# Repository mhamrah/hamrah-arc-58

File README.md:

# Hamrah Arc 58

A low-profile, split 58-input keyboard built around Kailh Choc v1 hotswap
switches, KEEBD Helios RP2040 controllers, per-key RGB, OLEDs, clickable
encoders, and a fully reversible PCB. The design keeps the approved Sofle Choc
6x4 column-staggered field and replaces the original bottom cluster with a
four-key inward/downward Arc thumb fan.

Each half has 29 press inputs:

- 24 column-staggered main keys;
- four Arc thumb keys; and
- one clickable rotary encoder.

## Layout preview

[Open the full-size SVG](output/keyboard-layout.svg)

## Geometry

All dimensions live in `layout.config.json`.

| Parameter | Value |
| --- | ---: |
| Main matrix pitch | 19.05 x 19.05 mm |
| Choc plate cutout | 14 x 14 mm |
| Specified Choc v1 keycap | 16.5 x 16.5 mm |
| Choc keys per half | 28 |
| Clickable encoders per half | 1 |
| EC11 body plate cutout | 12.5 x 12.5 mm |
| Encoder knob-to-C6 / knob-to-inner-edge gap | 9.17 mm / 9.17 mm |
| Thumb center spacing | 21.25 mm |
| T1 outward offset from C5/C6 midpoint | 1.0 mm |
| Conservative thumb envelope / minimum gap | 18 x 18 mm / 0.5 mm |
| Thumb key rotations | 10, 30, 45, 55 degrees |
| Mounting holes per half | 6 x 2.2 mm |

## Generate and verify

Node.js 18 or newer and KiCad 9 are required.

```sh
npm run generate
npm run verify
npm run generate:enclosures
```

Generation creates the mirrored layout, a US Letter 1:1 paper test, exact key
positions, and left/right top and bottom plate SVG/DXF files under `output/`.
Print the paper test at Actual Size / 100% and confirm its calibration bar is
exactly 50 mm before ordering plates.

`generate:enclosures` additionally creates vendor ZIP packages for 1.5 mm
acrylic top plates, 3 mm acrylic bottom plates, and a 6061-T6 machined aluminum
case under `output/manufacturing/`. It uses `uv` with Python 3.12 to run the
CadQuery solid-model generator. Material, tolerances, fit-coupon instructions,
and the nominal hardware stack are documented in
[`hardware/ENCLOSURES.md`](hardware/ENCLOSURES.md).

The single native PCB project is:

```text
hardware/kicad/arc58-reversible.kicad_pro
hardware/kicad/arc58-reversible.kicad_pcb
```

Order two copies of the same Rev Gamma PCB. In the assembled keyboard, the B.Cu
face points toward the keycaps on the left half and the F.Cu face points toward
the keycaps on the right half. Detailed component-side selection, verified pin
mapping, DRC status, and safety notes are in `hardware/README.md`; the pair BOM is
`hardware/BOM-REV-GAMMA.csv`.

Rev Gamma supersedes Rev Beta without changing any switch center, plate, or
case geometry. It moves D26-D29 into solder-friendly positions beside the four
thumb sockets, gives the inner D29 extra socket-body clearance, and reroutes
the affected reversible copper with no jumper. Rev Beta can be electrically
prototyped, but its inner thumb diode crowds the Choc socket and its outer
thumb diodes require awkward long reaches; do not reorder it.

Do not build or reorder Rev Alpha: it has no routed optical/package apertures
for per-key RGB, its TRRS jack points toward the encoder instead of the cable
exit, and its four thumb-switch axes are mirrored to the wrong physical
angles. Its 20.5 mm thumb centers also fail the conservative 18 x 18 mm
clearance requirement. Rev Alpha may be electrically bench-tested with every
RGB LED omitted and without an enclosure, but it does not implement the
intended keyboard.

## Prototype status

The routed board passes the repository's structural and electrical checks:
zero unrouted connections and zero shorts, crossings, or fabrication-clearance
violations. Its Edge.Cuts layer contains 28 closed 3.6 x 3.1 mm RGB apertures
per half, and the inner-edge TRRS jack/plate geometry provides a 10 mm cable
opening. The switch locator holes independently verify the assembled thumb
axes: +10, +30, +45, and +55 degrees on the B.Cu/left half, mirrored to -10,
-30, -45, and -55 degrees on the F.Cu/right half. T3 eases five degrees outward;
T4 eases fifteen degrees outward and its center moves 3.14 mm toward the side
and 2.59 mm upward from the former 70-degree position. The thumb centers remain
21.25 mm apart and preserve more than 0.5 mm nominal clearance for a
conservative 18 x 18 mm keycap envelope. The specified 16.5 x 16.5 mm caps
retain approximately 2.3 mm minimum clearance, with the T3-T4 gap increased to
approximately 3.44 mm. QMK is configured for
Helios, a one-wire TRRS split, OLED, encoder, and a 28+28 RGB Matrix. The
default firmware also compiles successfully against current upstream QMK; the
ignored local UF2 is generated at
`output/firmware/arc58-rev-gamma-default.uf2`.

This is still a prototype until a fabricated pair passes
`hardware/BRING-UP-CHECKLIST.md`. Choc switches plug into soldered hotswap
sockets; the switches themselves are not soldered to the PCB. Use a small
prototype order and verify switch/plate fit, diode and LED orientation, USB
current, every key, both encoders, both OLEDs, RGB, and the split link before a
larger run.

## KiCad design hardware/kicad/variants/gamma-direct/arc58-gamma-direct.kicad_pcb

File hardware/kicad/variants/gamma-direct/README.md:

# Arc 58 Gamma-D — direct RGB prototype

This variant removes the board-mounted U2 level shifter. It is a prototype for electrical qualification, not a production-qualified release. The original Gamma board is retained in the repository.

## Circuit

RP2040 GPIO0 / Pro Micro D3 / U1 pad 1 → RGB_MCU → R1 pad 1 → 330 ohm → R1 pad 2 → RGB_LED_IN → SW1 LED DIN pin 4 → remaining LED chain.

U2 and its footprint are removed. Copper replaces the U2 input/output connection. Obsolete supply/ground branch stubs were cleaned up and zones refilled. R1 remains 0603, nominal 330 ohm; 220 ohm is an acceptable substitute. No user-installed bypass jumper is needed. Do not substitute 10 kohm.

C1 remains available as an additional 100 nF supply bypass capacitor; it is optional for this direct variant. Populate C2, 47 uF / 10 V ceramic / 1206, for bulk RGB supply bypassing. The existing board still lacks per-LED bypass capacitors. LEDs remain on the 5 V rail. Existing firmware continues to use D3/GPIO0, and its brightness limit remains 32.

All other component positions and pad connections are unchanged. Existing plate and case geometry are retained. Silkscreen identifies this variant as GAMMA-D. BOM quantities cover both halves.

## How comparable keyboards avoid U2

The original Sofle RGB build guide specifies an ATmega32U4 Pro Micro or Elite-C. The usual 5 V versions already output 5 V logic, so they do not need a separate 3.3-to-5 V buffer. Using an RP2040 replacement changes this assumption.

Some 5 V addressable LEDs accept 3.3 V data in practice. Adafruit documents this behavior, including SK6812 devices, but it depends on device type, individual tolerances and operating conditions. A working prototype is useful evidence, not a guarantee for every future LED batch.

A design with guaranteed input compatibility can instead use an exact LED part whose specified input-high threshold accepts the controller's guaranteed output-high level, or obtain a shifted signal from a suitable controller pin. Neither is assumed in this variant. GPIO0 on the currently targeted controller remains the data source.

Sources:
- https://josefadamcik.github.io/SofleKeyboard/build_guide_rgb.html
- https://learn.adafruit.com/adafruit-neopixel-uberguide/logic-level
- https://docs.qmk.fm/drivers/ws2812

## Verification

- KiCad 10.0.5 DRC: zero violations and zero unconnected items; see DRC.json.
- Compared the original and variant: U2 is the only removed footprint; every remaining footprint position, orientation and pad net is preserved except the intended R1 pad 1 change to RGB_MCU. Both reversible SW1 DIN pads are preserved.
- Full repository structural check is NOT passing: both original Gamma and Gamma-D stop at the same existing D29 placement mismatch (130.839,137.603 mm versus expected 133.593,140.430 mm). This revision does not change D29. Checks after that failure have not run.
- No physical RGB, signal-integrity, temperature, or manufacturing qualification has been performed. No schematic exists in the source repository; this package contains the PCB project and BOM, not a new schematic.

Before ordering a batch, test the original board with the U2 2-to-4 jumper and R1 installed: that implements the same direct-drive concept. Confirm all LEDs on both halves across cold starts, different colors/animations, and normal USB power sources. If unreliable, keep the original buffered design or qualify a specified lower-threshold LED/controller solution.

## Files and repository

Open arc58-gamma-direct.kicad_pro in KiCad. The PCB includes its footprints; external 3D model libraries may be needed for 3D viewing. No Gerber manufacturing package is included.

Repository copy: hardware/kicad/variants/gamma-direct/.

The repository verifier accepts:

    python3 scripts/verify-kicad-board.py --direct-rgb --board hardware/kicad/variants/gamma-direct/arc58-gamma-direct.kicad_pcb

Use KiCad's Python environment for that command. For the DRC:

    kicad-cli pcb drc --format json --output direct-drc.json hardware/kicad/variants/gamma-direct/arc58-gamma-direct.kicad_pcb

The original generate:fab command still targets the original Gamma board.

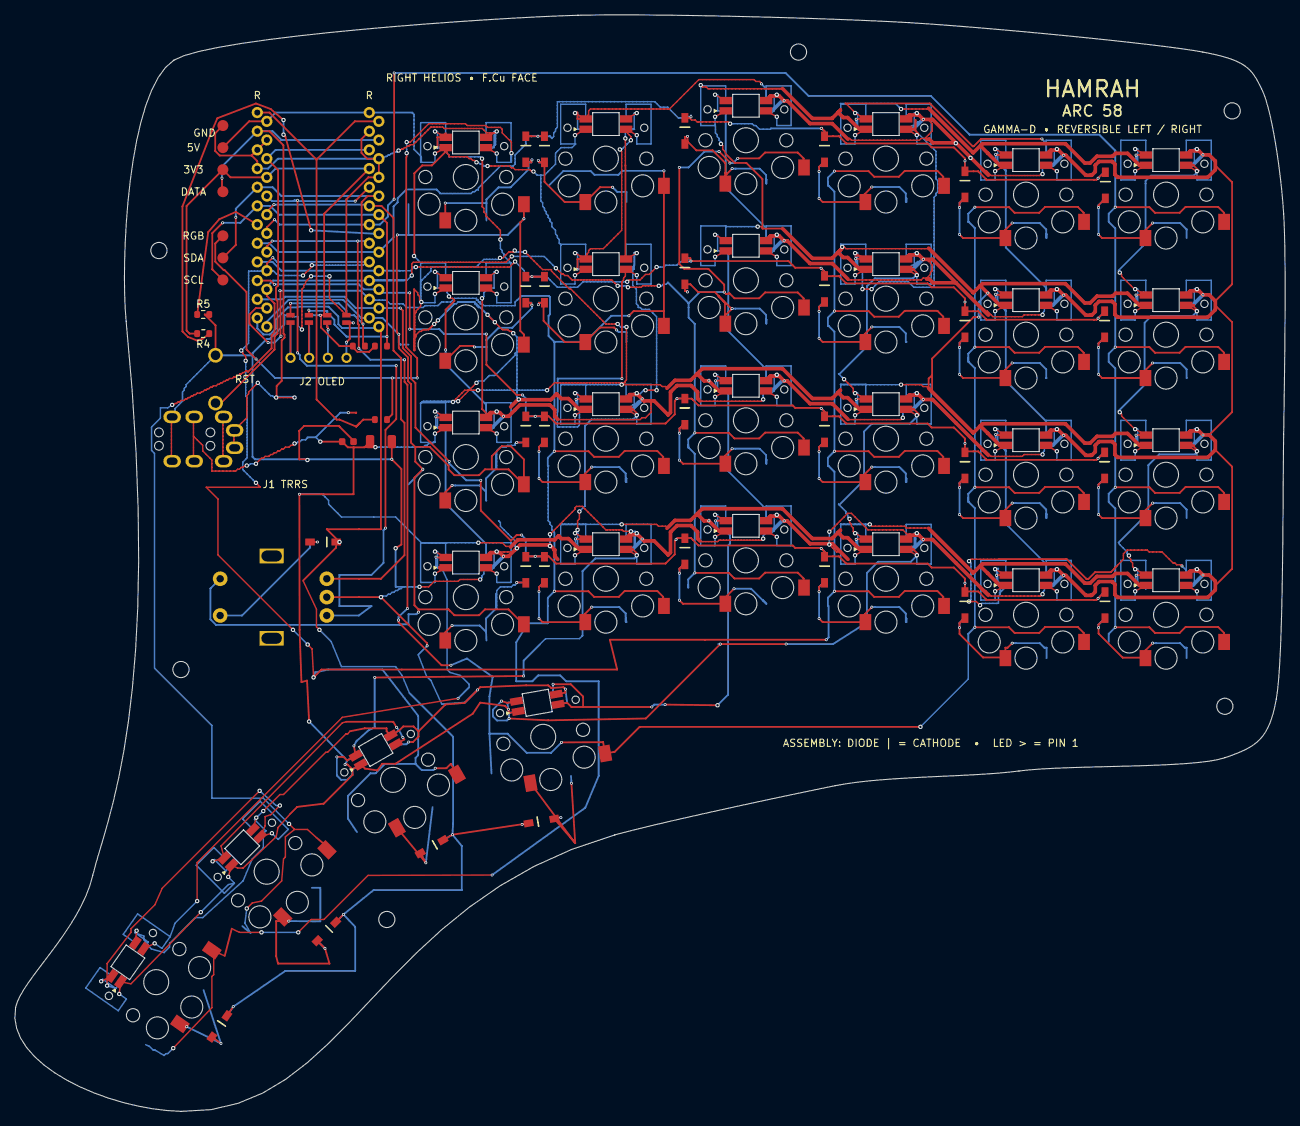
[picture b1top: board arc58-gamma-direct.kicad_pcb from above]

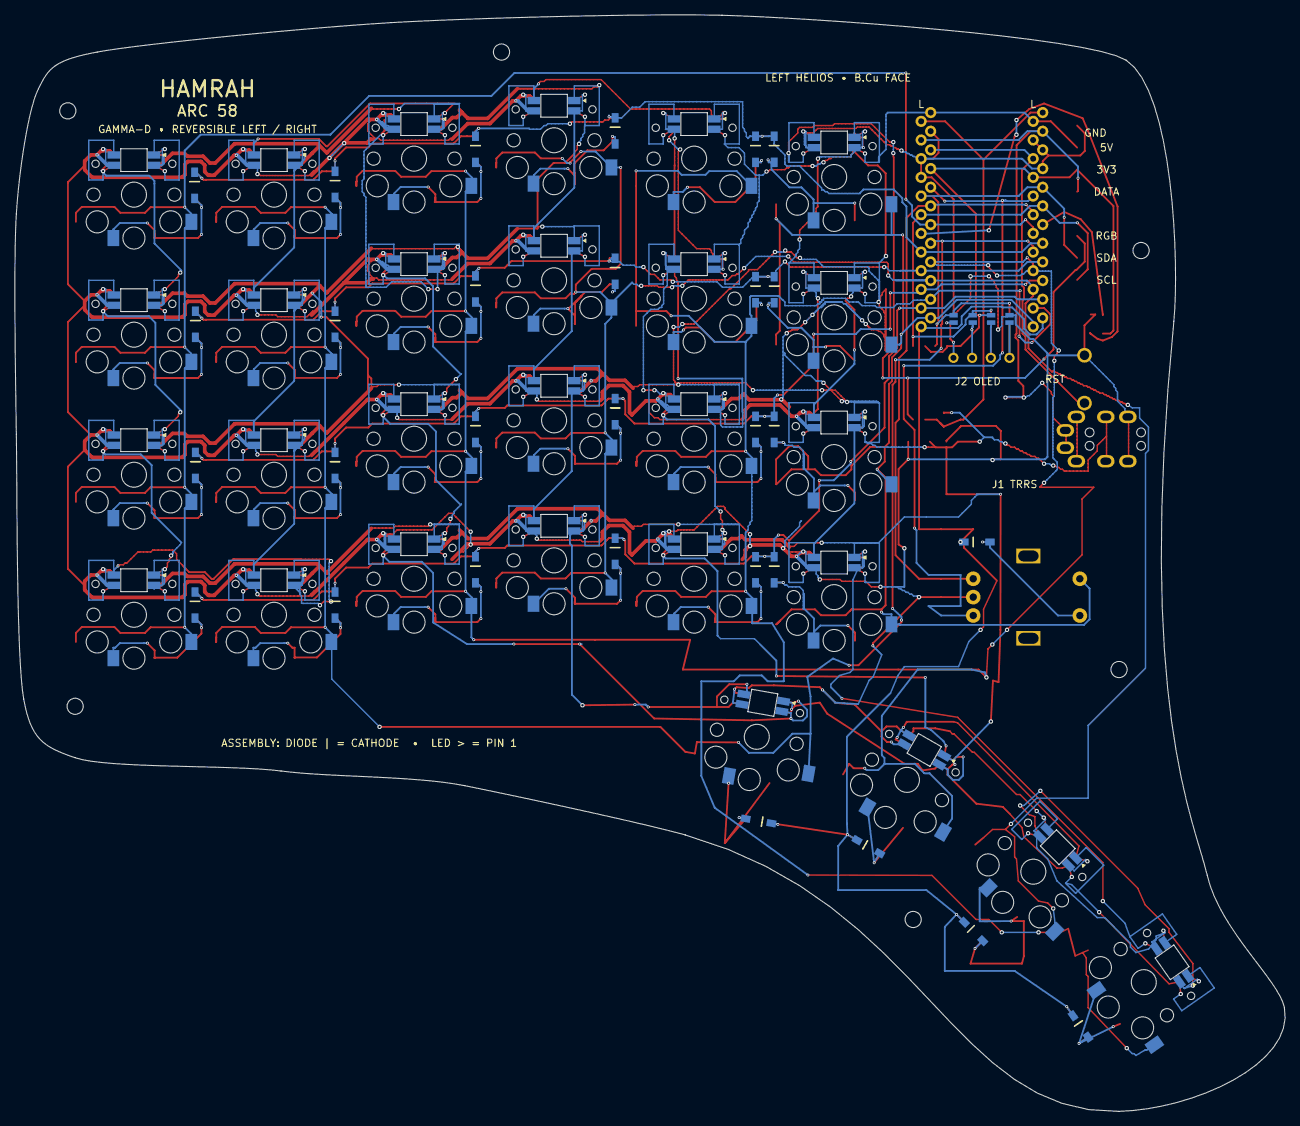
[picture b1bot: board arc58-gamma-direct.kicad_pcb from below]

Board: 2 copper layers, 172.8 x 149.2 mm, 90 parts (4 on the bottom side), 84 nets.

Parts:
C1: 100nF; C_0603_1608Metric
C2: 47uF 10V; C_1206_3216Metric
D1, D2, D3, D4, D5, D6, D7, D8, D9, D10, D11, D12, D13, D14, D15, D16, D17, D18, D19, D20, D21, D22, D23, D24, D25, D26, D27, D28, D29: D; Reversible_Diode_SOD123
H1, H2, H3, H4, H5, H6: MountingHole_2.2mm_M2
J1: MJ-4PP-9_Reversible; CON_MJ-4PP-9_Reversible
J2: SSD1306 OLED 128x32; OLED_4Pin
JP1, JP2, JP3, JP4, JP5, JP6, JP7, JP8: Jumper_NO_Small; Jumper
R1: 330R; R_0603_1608Metric
R2, R3: 4.7k; R_0603_1608Metric
R4, R5: 10k; R_0603_1608Metric
RST1: RESET; TACT_SWITCH_TVBP06
SW1, SW2, SW3, SW4, SW5, SW6, SW7, SW8, SW9, SW10, SW11, SW12, SW13, SW14, SW15, SW16, SW17, SW18, SW19, SW20, SW21, SW22, SW23, SW24, SW26, SW27, SW28, SW29: SW_PUSH_LED; Sofle_Choc_Hotswap_SK6812MINI-E_Reversible
SW25: EC11_Clickable_H20mm_T18; RotaryEncoder_Alps_EC11E-Switch_Vertical_H20mm-keebio_modif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
TP1, TP2, TP3, TP4, TP6, TP7, TP8: TestPoint_Pad_D1.5mm
U1: KEEBD Helios RP2040; ProMicro

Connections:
COL0: SW6.6, SW12.6, SW18.6, SW24.6, U1.18
COL1: SW5.6, SW11.6, SW17.6, SW23.6, SW29.6, U1.17
COL2: SW4.6, SW10.6, SW16.6, SW22.6, SW28.6, U1.16
COL3: SW3.6, SW9.6, SW15.6, SW21.6, SW27.6, U1.15
COL4: SW2.6, SW8.6, SW14.6, SW20.6, SW26.6, U1.14
COL5: SW1.6, SW7.6, SW13.6, SW19.6, SW25.S1, U1.13
ENC_A: SW25.A, U1.20
ENC_B: SW25.B, U1.19
GND: C1.2, C2.2, J1.S, JP1.2, JP8.2, R5.2, RST1.1, SW1.3, SW2.3, SW3.3, SW4.3, SW5.3, SW6.3, SW7.3, SW8.3, SW9.3, SW10.3, SW11.3, SW12.3, SW13.3, SW14.3, SW15.3, SW16.3, SW17.3, SW18.3, SW19.3, SW20.3, SW21.3, SW22.3, SW23.3, SW24.3, SW25.C, SW26.3, SW27.3, SW28.3, SW29.3, TP1.1, U1.3, U1.4, U1.23
HAND_L: R4.1, U1.L7
HAND_R: R5.1, U1.7
KEY_ENC: D25.2, SW25.S2
unnamed: D1.2, SW1.5
unnamed: D2.2, SW2.5
unnamed: D3.2, SW3.5
unnamed: D4.2, SW4.5
unnamed: D5.2, SW5.5
unnamed: D6.2, SW6.5
unnamed: D7.2, SW7.5
unnamed: D8.2, SW8.5
unnamed: D9.2, SW9.5
unnamed: D10.2, SW10.5
unnamed: D11.2, SW11.5
unnamed: D12.2, SW12.5
unnamed: D13.2, SW13.5
unnamed: D14.2, SW14.5
unnamed: D15.2, SW15.5
unnamed: D16.2, SW16.5
unnamed: D17.2, SW17.5
unnamed: D18.2, SW18.5
unnamed: D19.2, SW19.5
unnamed: D20.2, SW20.5
unnamed: D21.2, SW21.5
unnamed: D22.2, SW22.5
unnamed: D23.2, SW23.5
unnamed: D24.2, SW24.5
unnamed: D26.2, SW26.5
unnamed: D27.2, SW27.5
unnamed: D28.2, SW28.5
unnamed: D29.2, SW29.5
unnamed: J2.1, JP4.1, JP8.1
unnamed: J2.2, JP3.1, JP7.1
unnamed: J2.3, JP2.1, JP6.1
unnamed: J2.4, JP1.1, JP5.1
unnamed: SW1.2, SW7.4
unnamed: SW2.2, SW3.4
unnamed: SW2.4, SW8.2
unnamed: SW3.2, SW9.4
unnamed: SW4.2, SW5.4
unnamed: SW4.4, SW10.2
unnamed: SW10.4, SW16.2
unnamed: SW11.2, SW17.4
unnamed: SW5.2, SW11.4
unnamed: SW6.4, SW12.2
unnamed: SW12.4, SW18.2
unnamed: SW13.2, SW19.4
unnamed: SW7.2, SW13.4
unnamed: SW8.4, SW14.2
unnamed: SW14.4, SW20.2
unnamed: SW15.2, SW21.4
unnamed: SW9.2, SW15.4
unnamed: SW16.4, SW22.2
unnamed: SW17.2, SW23.4
unnamed: SW18.4, SW24.2
unnamed: SW19.2, SW26.4
unnamed: SW20.4, SW28.2
unnamed: SW21.2, SW29.4
unnamed: SW23.2, SW24.4
unnamed: SW26.2, SW27.4
unnamed: SW27.2, SW28.4
unnamed: SW22.4, SW29.2
OLED_SCL: JP3.2, JP6.2, R3.2, TP8.1, U1.6
OLED_SDA: JP4.2, JP5.2, R2.2, TP7.1, U1.5
RESET: RST1.2, U1.22
RGB_LED_IN: R1.2, SW1.4, TP6.1
RGB_MCU: R1.1, U1.1
ROW0: D1.1, D2.1, D3.1, D4.1, D5.1, D6.1, U1.8
ROW1: D7.1, D8.1, D9.1, D10.1, D11.1, D12.1, U1.9
ROW2: D13.1, D14.1, D15.1, D16.1, D17.1, D18.1, U1.10
ROW3: D19.1, D20.1, D21.1, D22.1, D23.1, D24.1, U1.11
ROW4: D25.1, D26.1, D27.1, D28.1, D29.1, U1.12
SPLIT_DATA: J1.T, TP4.1, U1.2
VBUS: C1.1, C2.1, J1.R2, SW1.1, SW2.1, SW3.1, SW4.1, SW5.1, SW6.1, SW7.1, SW8.1, SW9.1, SW10.1, SW11.1, SW12.1, SW13.1, SW14.1, SW15.1, SW16.1, SW17.1, SW18.1, SW19.1, SW20.1, SW21.1, SW22.1, SW23.1, SW24.1, SW26.1, SW27.1, SW28.1, SW29.1, TP2.1, U1.24
VCC3V3: JP2.2, JP7.2, R2.1, R3.1, R4.2, TP3.1, U1.21

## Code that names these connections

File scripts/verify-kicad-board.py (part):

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if split.get("handedness", {}).get("pin") != "D4":
    fail("QMK handedness pin must match the isolated U1 D4 header positions")
if keyboard.get("ws2812", {}).get("pin") != "D3":
    fail("QMK WS2812 pin must match U1 RGB_MCU on D3")
if keyboard.get("rgb_matrix", {}).get("split_count") != [28, 28]:
    fail("QMK RGB matrix must contain 28 LEDs per half")
for feature in ("encoder", "oled", "rgb_matrix"):
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if keyboard.get("encoder", {}).get("rotary") != [
    {"pin_a": "F4", "pin_b": "F5", "resolution": 2}
]:
    fail("QMK left encoder pins do not match U1 ENC_A/ENC_B")
if split.get("encoder", {}).get("right", {}).get("rotary") != [
    {"pin_a": "F5", "pin_b": "F4", "resolution": 2}
]:
    fail("QMK right encoder pins must reverse for the mirrored assembly")
config_h = (FIRMWARE / "config.h").read_text()
if "#define I2C1_SDA_PIN D1" not in config_h or "#define I2C1_SCL_PIN D0" not in config_h:
    fail("QMK OLED I2C pins do not match U1 OLED_SDA/OLED_SCL")
if "SPLIT_HAND_PIN_LOW_IS_LEFT" in config_h:
    fail("QMK handedness polarity must remain high=left and low=right")
if "CONVERT_TO = elite_pi" not in (FIRMWARE / "rules.mk").read_text():
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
